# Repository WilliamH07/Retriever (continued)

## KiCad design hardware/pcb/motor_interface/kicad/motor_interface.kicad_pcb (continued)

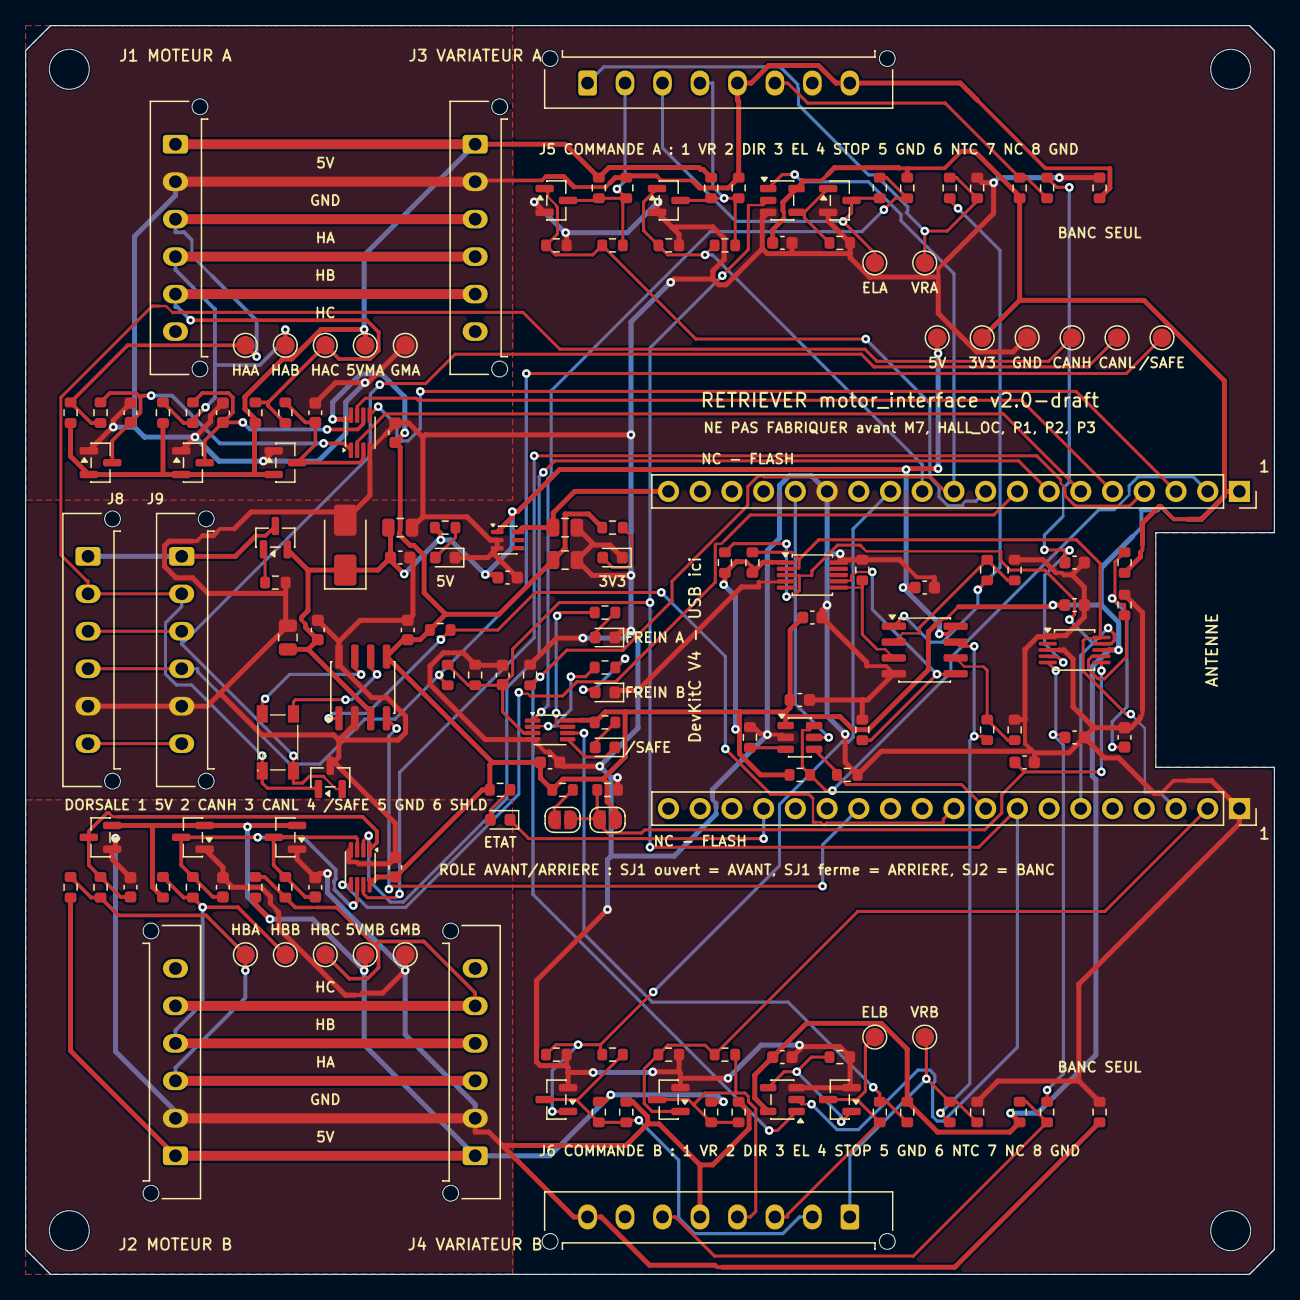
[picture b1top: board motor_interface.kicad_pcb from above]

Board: 4 copper layers, 100.0 x 100.0 mm, 167 parts (0 on the bottom side), 83 nets.

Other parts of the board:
H1, H2, H3, H4: M3; MountingHole_3.2mm_M3

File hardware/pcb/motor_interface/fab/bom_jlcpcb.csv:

Comment,Designator,Footprint,LCSC Part #
10uF,"C1,C4,C5",C_0805_2012Metric,C15850
100nF,"C10,C11,C113,C115,C12,C13,C14,C143,C145,C15,C16,C17,C18,C2,C7,C8",C_0603_1608Metric,C14663
10nF/100V,"C101,C105,C109,C151,C155,C159",C_0603_1608Metric,C43253
1uF,C3,C_0603_1608Metric,C15849
4.7uF,C6,C_0805_2012Metric,C1779
100pF,C9,C_0603_1608Metric,C14858
SMAJ6.0A,D1,D_SMA,C223993
BAT54S,"D101,D105,D109,D151,D155,D159",SOT-23,C47546
Everlight 19-217/GHC,"D2,D3",LED_0603_1608Metric,C72043
NUP2105L,D4,SOT-23,C14486
Hubei KENTO KT-0603R,"D5,D6,D7",LED_0603_1608Metric,C2286
ETAT,D8,LED_0603_1608Metric,C72041
Molex 43650-0615,"J1,J2,J3,J4,J8,J9",Molex_Micro-Fit_3.0_43650-0615_1x06_P3.00mm_Vertical,C505231
ACT45B-510,L1,IND-SMD_4P-L4.5-W3.2-TL,C76584
AO3401A,Q1,SOT-23,C15127
AO3400A,"Q101,Q106,Q111,Q131,Q136,Q141",SOT-23,C20917
10k,"R1,R14,R142,R145,R17,R172,R175,R20,R21,R22,R4",R_0603_1608Metric,C25804
100k,"R10,R131,R136,R141,R15,R161,R166,R171,R18,R7,R9",R_0603_1608Metric,C25803
2.2k,"R101,R102,R105,R106,R109,R110,R151,R152,R155,R156,R159,R160",R_0603_1608Metric,C4190
4.7k,"R11,R12",R_0603_1608Metric,C23162
15k,"R13,R16",R_0603_1608Metric,C22809
1M,"R143,R173,R6",R_0603_1608Metric,C22935
100Ω,"R144,R174",R_0603_1608Metric,C22775
3.3k,"R146,R176",R_0603_1608Metric,C22978
1k,"R147,R177,R2,R23,R24,R25,R26,R3",R_0603_1608Metric,C21190
20k,R19,R_0603_1608Metric,C4184
47k,R5,R_0603_1608Metric,C25819
6.8k,R8,R_0603_1608Metric,C23212
LM66100DCKR,U1,SOT-363_SC-70-6,C2869734
SN74LVC3G17DCUR,"U10,U11,U7",VSSOP-8_2.3x2mm_P0.5mm,C68245
SN74LVC1G08DBVR,"U12,U13",SOT-23-5,C7666
TCAN1042HVDR,U2,SOIC-8_3.9x4.9mm_P1.27mm,C127869
TPL5010DDCR,U3,SOT-23-6,C473912
MCP4728-E/UN,U4,MSOP-10_3x3mm_P0.5mm,C108207
TLV9062IDR,U5,SOIC-8_3.9x4.9mm_P1.27mm,C398355
ADS1115IDGSR,U6,TSSOP-10_3x3mm_P0.5mm,C37593
